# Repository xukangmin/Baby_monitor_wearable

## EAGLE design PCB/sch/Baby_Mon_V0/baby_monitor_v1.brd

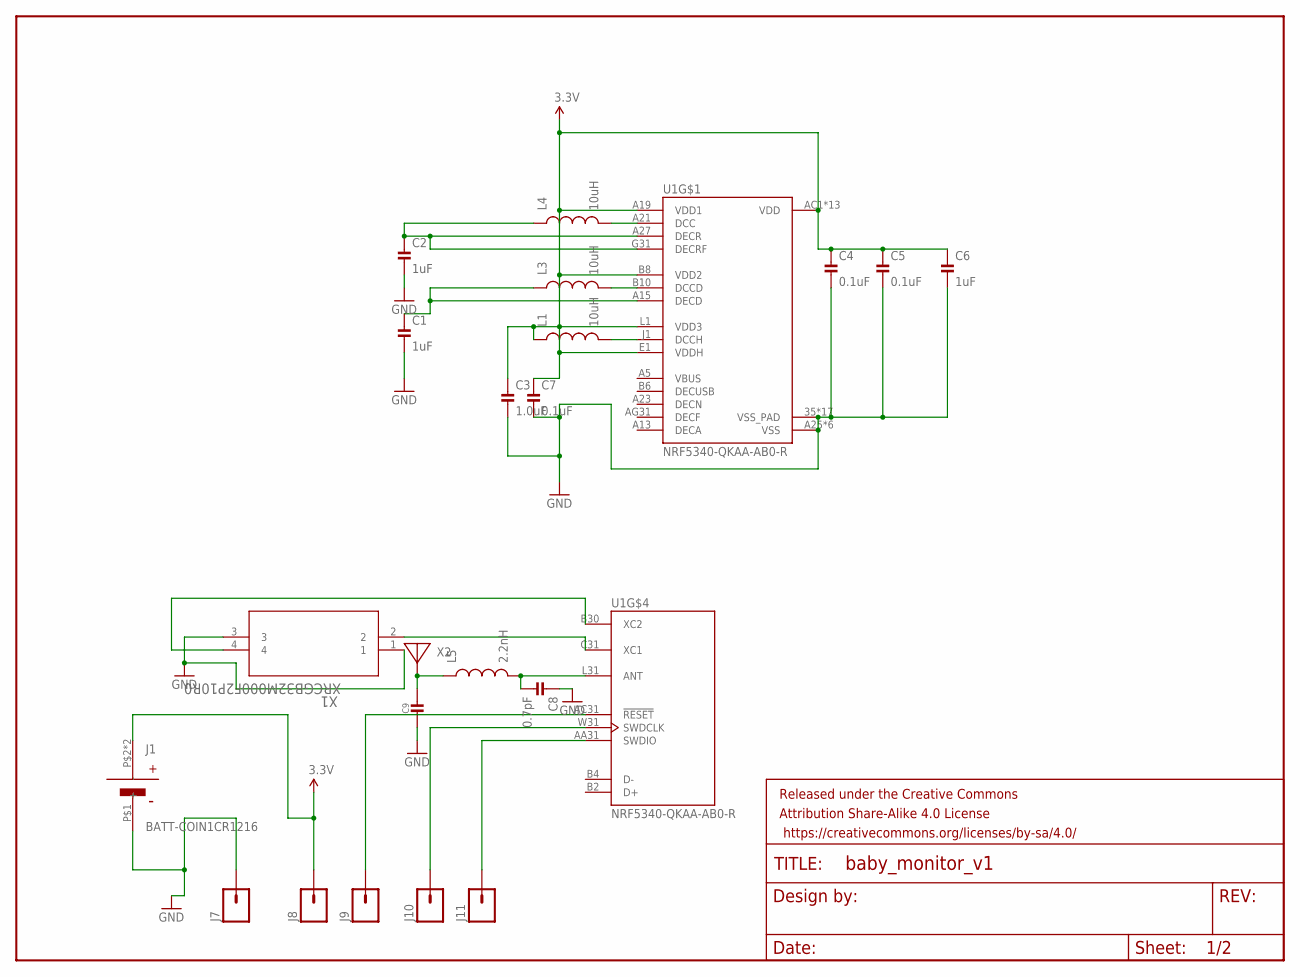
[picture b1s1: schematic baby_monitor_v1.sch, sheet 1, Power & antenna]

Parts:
C1, C2, C6: 1uF; MICROBUILDER__0402MP
C3: 1.0uF; MICROBUILDER__0402MP
C4, C5, C7: 0.1uF; MICROBUILDER__0402MP
C8: 0.7pF; MICROBUILDER__0402MP
C9: MICROBUILDER_CAP_CERAMIC_0402MP; MICROBUILDER__0402MP
FRAME1: FRAME-LETTERNO_PACKAGE; DUMMY
J1: BATT-COIN1CR1216; BC-2017-TR
J7, J8, J9, J10, J11: M01TINY; 1X01_TINY
L1, L3, L4: 10uH; NORDIC_MISC_RESC0603_N
L5: 2.2nH; NORDIC_MISC_RESC0402_N
U1: NRF5340-QKAA-AB0-R; XCVR_NRF5340-QKAA-AB0-R
X1: XRCGB32M000F2P10R0; XTAL_SON4_1P6X2P0_MUR
X2: ADAFRUIT_WIRELESS_ANTENNA_JOHANSON_2450AT18B100; ADAFRUIT_WIRELESS_ANT_2450AT18B100

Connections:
3.3V: C3.1, C4.1, C5.1, C6.1, C7.1, J1.P$2 (+), J1.P$3 (+), J8.P$1, L1.1, U1.A19 (VDD1), U1.AC1 (VDD), U1.AG1 (VDD), U1.AJ31 (VDD), U1.AL3 (VDD), U1.AL7 (VDD), U1.AL11 (VDD), U1.AL17 (VDD), U1.AL25 (VDD), U1.B8 (VDD2), U1.B28 (VDD), U1.C1 (VDD), U1.E1 (VDDH), U1.E31 (VDD), U1.L1 (VDD3), U1.N31 (VDD), U1.U1 (VDD); also elsewhere on the board
DECA: U1.A13 (DECA)
DECF: U1.AG31 (DECF)
DECN: U1.A23 (DECN)
DECUSB: U1.B6 (DECUSB)
GND: C1.2, C2.2, C3.2, C4.2, C5.2, C6.2, C7.2, C8.1, C9.2, J1.P$1 (-), J7.P$1, U1.35 (VSS_PAD), U1.36 (VSS_PAD), U1.37 (VSS_PAD), U1.38 (VSS_PAD), U1.39 (VSS_PAD), U1.40 (VSS_PAD), U1.41 (VSS_PAD), U1.43 (VSS_PAD), U1.44 (VSS_PAD), U1.45 (VSS_PAD), U1.46 (VSS_PAD), U1.47 (VSS_PAD), U1.48 (VSS_PAD), U1.49 (VSS_PAD), U1.50 (VSS_PAD), U1.51 (VSS_PAD), U1.104 (VSS_PAD), U1.A25 (VSS), U1.B12 (VSS), U1.B26 (VSS), U1.G1 (VSS), U1.H2 (VSS), U1.J31 (VSS), X1.1, X1.3; also elsewhere on the board
unnamed: L4.2, U1.A21 (DCC)
unnamed: L1.2, U1.J1 (DCCH)
unnamed: L3.2, U1.B10 (DCCD)
unnamed: C2.1, L4.1, U1.A27 (DECR), U1.G31 (DECRF)
unnamed: C1.1, L3.1, U1.A15 (DECD)
unnamed: U1.C31 (XC1), X1.2
unnamed: U1.B30 (XC2), X1.4
unnamed: C8.2, L5.2, U1.L31 (ANT)
unnamed: C9.1, L5.1, X2.FP
RESET: J9.P$1, U1.AC31 (!RESET)
SWDCLK: J10.P$1, U1.W31 (SWDCLK)
SWDIO: J11.P$1, U1.AA31 (SWDIO)
VBUS: U1.A5 (VBUS)

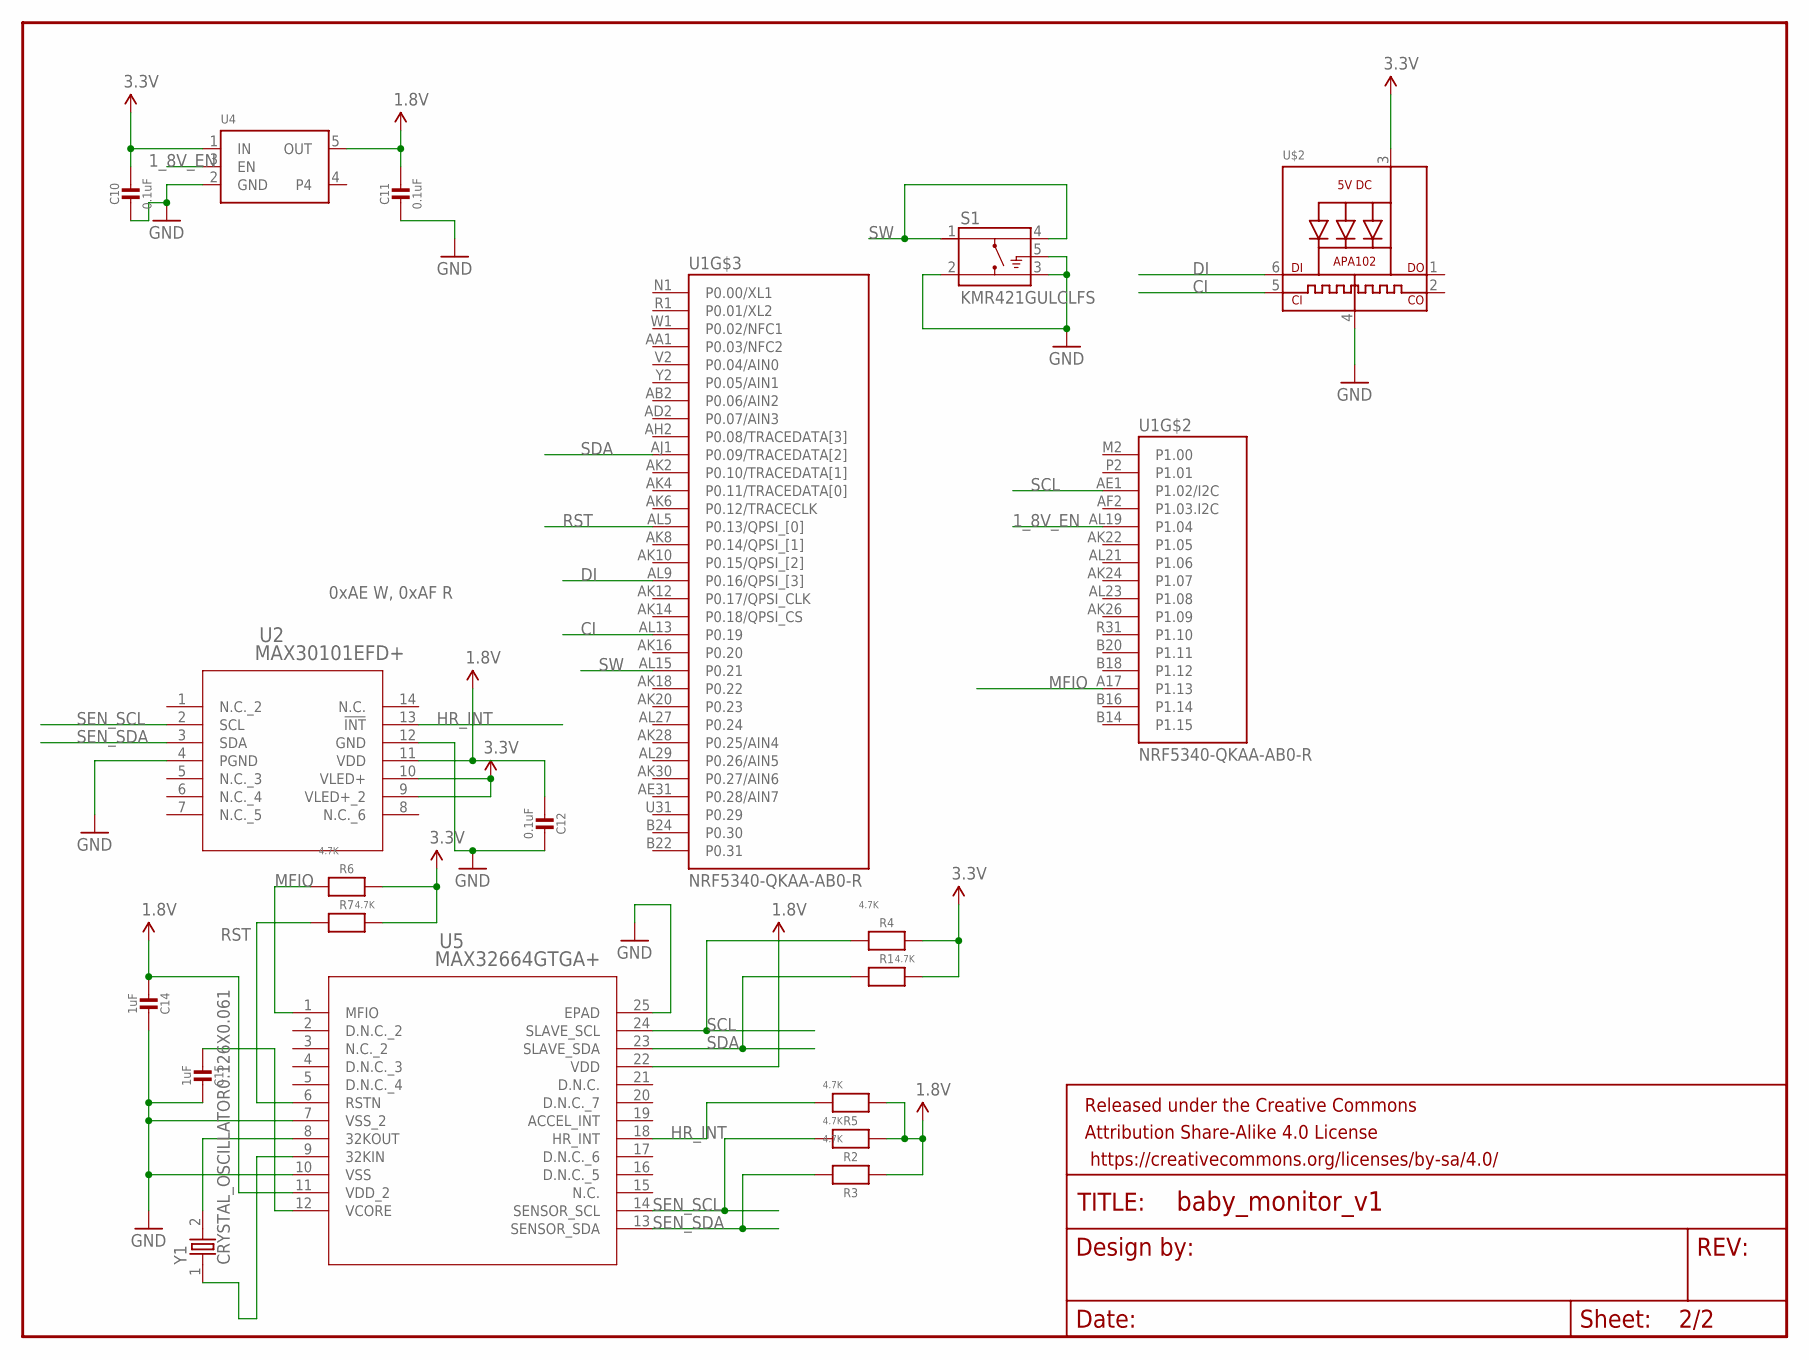
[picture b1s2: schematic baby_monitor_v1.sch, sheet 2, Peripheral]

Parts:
C10, C11, C12: 0.1uF; MICROBUILDER__0402MP
C14, C15: 1uF; MICROBUILDER__0402MP
FRAME2: FRAME-LETTERNO_PACKAGE; DUMMY
R1, R2, R3, R4, R5, R6, R7: 4.7K; MICROBUILDER__0402MP
S1: KMR421GULCLFS; SW_KMR421GULCLFS
U1: NRF5340-QKAA-AB0-R; XCVR_NRF5340-QKAA-AB0-R
U2: MAX30101EFD+; 21-0880B_MXM
U4: MICROBUILDER_VREG_SOT23-5; MICROBUILDER_SOT23-5
U5: MAX32664GTGA+; 21-100264_90-100089_MXM
U$2: MICROBUILDER_APA1022020; MICROBUILDER_APA102_2020
Y1: CRYSTAL_OSCILLATOR0.126X0.061; QUARTZ

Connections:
1.8V: C11.1, C12.2, C14.2, R2.1, R3.1, R5.1, U2.11 (VDD), U4.5 (OUT), U5.11 (VDD_2), U5.22 (VDD)
1_8V_EN: U1.AL19 (P1.04), U4.3 (EN)
3.3V: C10.1, R1.2, R4.2, R6.2, R7.2, U2.9 (VLED+_2), U2.10 (VLED+), U4.1 (IN), U$2.3 (VDD); also elsewhere on the board
CI: U1.AL13 (P0.19), U$2.5 (CKI)
DECA: U1.A13 (DECA)
DECF: U1.AG31 (DECF)
DECN: U1.A23 (DECN)
DECUSB: U1.B6 (DECUSB)
DI: U1.AL9 (P0.16/QPSI_[3]), U$2.6 (DI)
GND: C10.2, C11.2, C12.1, C14.1, C15.1, S1.2, S1.3, S1.5 (G), U2.4 (PGND), U2.12 (GND), U4.2 (GND), U5.7 (VSS_2), U5.10 (VSS), U5.25 (EPAD), U$2.4 (GND); also elsewhere on the board
HR_INT: R5.2, U2.13 (!INT), U5.18 (HR_INT)
MFIO: R6.1, U1.A17 (P1.13), U5.1 (MFIO)
unnamed: C15.2, U5.12 (VCORE)
unnamed: U5.8 (32KOUT), Y1.2
unnamed: U5.9 (32KIN), Y1.1
RST: R7.1, U1.AL5 (P0.13/QPSI_[0]), U5.6 (RSTN)
SCL: R4.1, U1.AE1 (P1.02/I2C), U5.24 (SLAVE_SCL)
SDA: R1.1, U1.AJ1 (P0.09/TRACEDATA[2]), U5.23 (SLAVE_SDA)
SEN_SCL: R2.2, U2.2 (SCL), U5.14 (SENSOR_SCL)
SEN_SDA: R3.2, U2.3 (SDA), U5.13 (SENSOR_SDA)
SW: S1.1, S1.4, U1.AL15 (P0.21)
VBUS: U1.A5 (VBUS)

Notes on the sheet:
0xAE W, 0xAF R

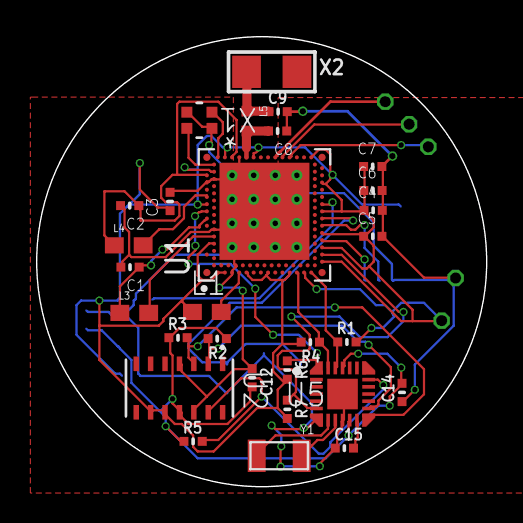
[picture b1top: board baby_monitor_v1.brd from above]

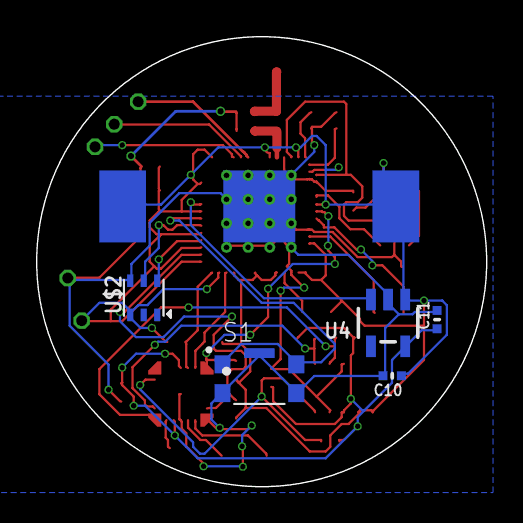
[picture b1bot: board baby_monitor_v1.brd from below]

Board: 2 copper layers, 25.0 x 25.0 mm, 42 parts (6 on the bottom side), 29 nets.

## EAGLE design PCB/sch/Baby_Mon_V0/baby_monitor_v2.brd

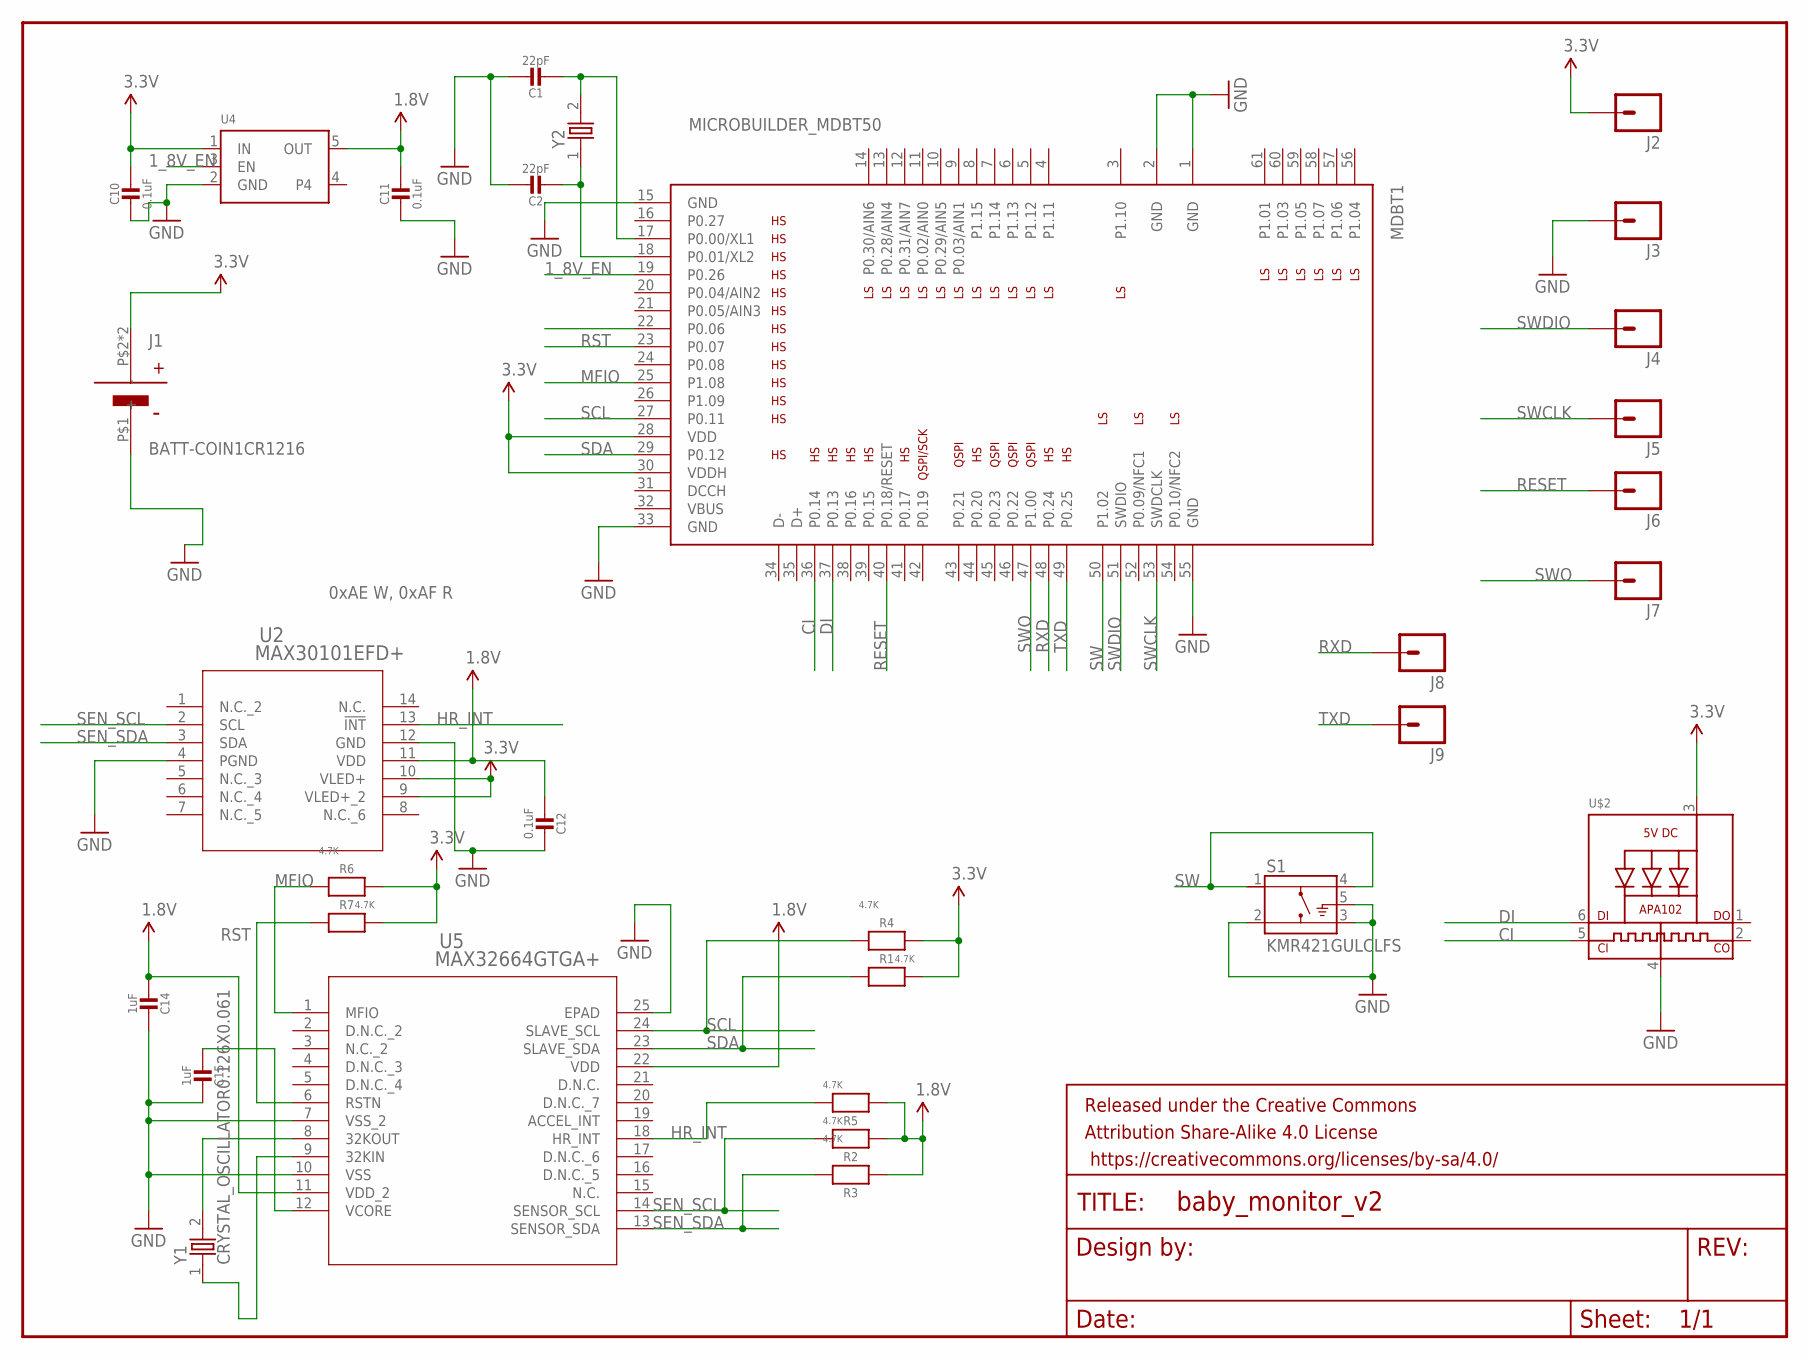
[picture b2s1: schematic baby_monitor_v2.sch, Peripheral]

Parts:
C1, C2: 22pF; MICROBUILDER__0402MP
C10, C11, C12: 0.1uF; MICROBUILDER__0402MP
C14, C15: 1uF; MICROBUILDER__0402MP
FRAME2: FRAME-LETTERNO_PACKAGE; DUMMY
J1: BATT-COIN1CR1216; BC-2017-TR
J2, J3, J4, J5, J6, J7: M01TINY; 1X01_TINY
J8, J9: M01TINY_SMD_EXT; 1X01_SMD_TINY_EXT
MDBT1: MICROBUILDER_MDBT50
R1, R2, R3, R4, R5, R6, R7: 4.7K; MICROBUILDER__0402MP
S1: KMR421GULCLFS; SW_KMR421GULCLFS
U2: MAX30101EFD+; 21-0880B_MXM
U4: MICROBUILDER_VREG_SOT23-5; MICROBUILDER_SOT23-5
U5: MAX32664GTGA+; 21-100264_90-100089_MXM
U$2: MICROBUILDER_APA1022020; MICROBUILDER_APA102_2020
Y1, Y2: CRYSTAL_OSCILLATOR0.126X0.061; QUARTZ

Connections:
1.8V: C11.1, C12.2, C14.2, R2.1, R3.1, R5.1, U2.11 (VDD), U4.5 (OUT), U5.11 (VDD_2), U5.22 (VDD)
1_8V_EN: MDBT1.19 (P0.26), U4.3 (EN)
3.3V: C10.1, J1.P$2 (+), J1.P$3 (+), J2.P$1, MDBT1.28 (VDD), MDBT1.30 (VDDH), R1.2, R4.2, R6.2, R7.2, U2.9 (VLED+_2), U2.10 (VLED+), U4.1 (IN), U$2.3 (VDD)
CI: MDBT1.36 (P0.14), U$2.5 (CKI)
DI: MDBT1.37 (P0.13), U$2.6 (DI)
GND: C1.1, C2.1, C10.2, C11.2, C12.1, C14.1, C15.1, J1.P$1 (-), J3.P$1, MDBT1.1 (GND), MDBT1.2 (GND), MDBT1.15 (GND), MDBT1.33 (GND), MDBT1.55 (GND), S1.2, S1.3, S1.5 (G), U2.4 (PGND), U2.12 (GND), U4.2 (GND), U5.7 (VSS_2), U5.10 (VSS), U5.25 (EPAD), U$2.4 (GND)
HR_INT: R5.2, U2.13 (!INT), U5.18 (HR_INT)
MFIO: MDBT1.25 (P1.08), R6.1, U5.1 (MFIO)
unnamed: C1.2, MDBT1.17 (P0.00/XL1), Y2.2
unnamed: C2.2, MDBT1.18 (P0.01/XL2), Y2.1
unnamed: C15.2, U5.12 (VCORE)
unnamed: U5.8 (32KOUT), Y1.2
unnamed: U5.9 (32KIN), Y1.1
RESET: J6.P$1, MDBT1.40 (P0.18/RESET)
RST: MDBT1.23 (P0.07), R7.1, U5.6 (RSTN)
RXD: J8.P$1, MDBT1.48 (P0.24)
SCL: MDBT1.27 (P0.11), R4.1, U5.24 (SLAVE_SCL)
SDA: MDBT1.29 (P0.12), R1.1, U5.23 (SLAVE_SDA)
SEN_SCL: R2.2, U2.2 (SCL), U5.14 (SENSOR_SCL)
SEN_SDA: R3.2, U2.3 (SDA), U5.13 (SENSOR_SDA)
SW: MDBT1.50 (P1.02), S1.1, S1.4
SWCLK: J5.P$1, MDBT1.53 (SWDCLK)
SWDIO: J4.P$1, MDBT1.51 (SWDIO)
SWO: J7.P$1, MDBT1.47 (P1.00)
TXD: J9.P$1, MDBT1.49 (P0.25)

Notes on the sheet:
0xAE W, 0xAF R

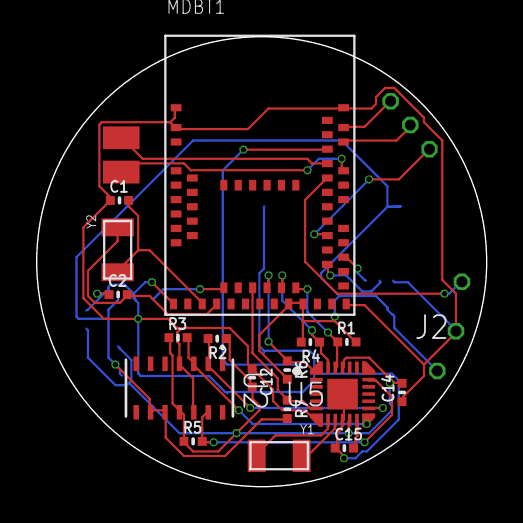
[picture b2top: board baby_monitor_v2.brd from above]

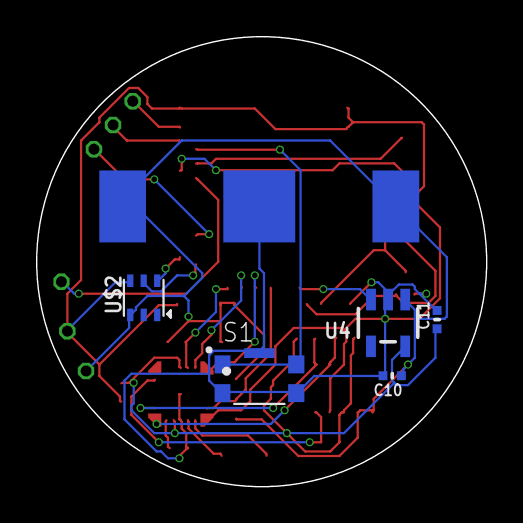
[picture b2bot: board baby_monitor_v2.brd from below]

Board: 2 copper layers, 25.0 x 25.0 mm, 32 parts (6 on the bottom side), 25 nets.

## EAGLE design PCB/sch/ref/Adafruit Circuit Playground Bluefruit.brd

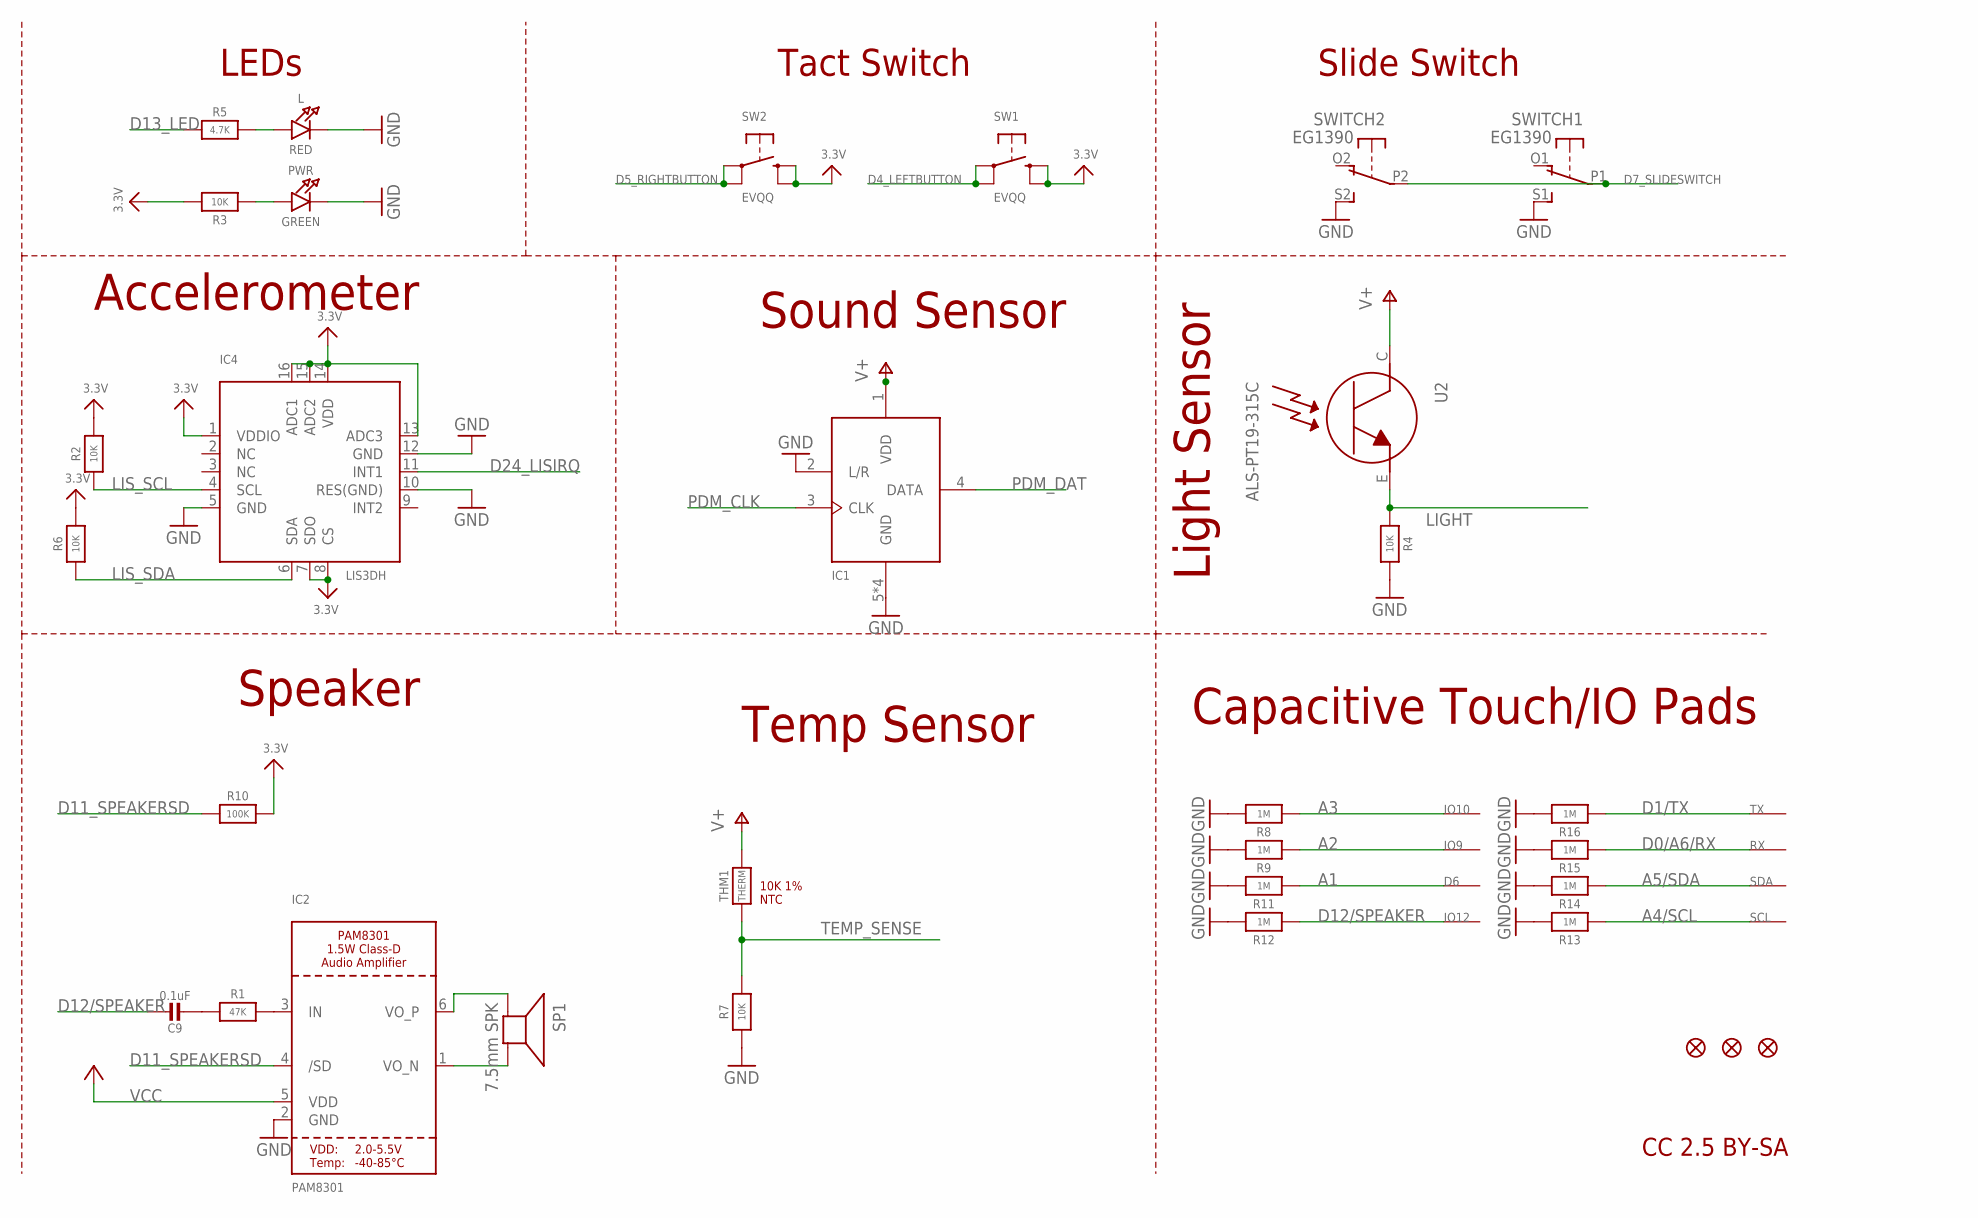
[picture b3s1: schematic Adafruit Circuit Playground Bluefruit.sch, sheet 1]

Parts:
C9: 0.1uF; 0603-NO
D6: SEWTAP-ALLIGATOR; SEWALLI
IC1: MIC_PDM; SPK0415HM4H
IC2: PAM8301; SOT23-6
IC4: LIS3DH; LGA16_3X3MM
IO9, IO10, IO12: SEWTAP-ALLIGATOR; SEWALLI
L: RED; CHIPLED_0603_NOOUTLINE
PWR: GREEN; CHIPLED_0603_NOOUTLINE
R1: 47K; 0603-NO
R2, R3, R4, R6, R7: 10K; 0603-NO
R5: 4.7K; 0603-NO
R8, R9, R11, R12, R13, R14, R15, R16: 1M; 0603-NO
R10: 100K; 0603-NO
RX: SEWTAP-ALLIGATOR; SEWALLI
SCL: SEWTAP-ALLIGATOR; SEWALLI
SDA: SEWTAP-ALLIGATOR; SEWALLI
SP1: 7.5mm SPK; BUZZER_SMT_7.5MM
SW1, SW2: EVQQ; EVQ-Q2_SMALLER
SWITCH: EG1390
THM1: THERM; _0402
TX: SEWTAP-ALLIGATOR; SEWALLI
U2: ALS-PT19-315C
U$2, U$3, U$6: FIDUCIAL_1MM

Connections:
3.3V: IC4.1 (VDDIO), IC4.7 (SDO), IC4.8 (CS), IC4.13 (ADC3), IC4.14 (VDD), IC4.15 (ADC2), IC4.16 (ADC1), R2.2, R3.2, R6.2, R10.2, SW1.B (S), SW1.B' (S1), SW2.B (S), SW2.B' (S1); also elsewhere on the board
A1: D6.P$1, R11.1; also elsewhere on the board
A2: IO9.P$1, R9.1; also elsewhere on the board
A3: IO10.P$1, R8.1; also elsewhere on the board
A4/SCL: R13.1, SCL.P$1; also elsewhere on the board
A5/SDA: R14.1, SDA.P$1; also elsewhere on the board
D0/A6/RX: R15.1, RX.P$1; also elsewhere on the board
D1/TX: R16.1, TX.P$1; also elsewhere on the board
D4_LEFTBUTTON: SW1.A, SW1.A' (P1); also elsewhere on the board
D5_RIGHTBUTTON: SW2.A, SW2.A' (P1); also elsewhere on the board
D7_SLIDESWITCH: SWITCH.P1, SWITCH.P2; also elsewhere on the board
D11_SPEAKERSD: IC2.4 (/SD), R10.1; also elsewhere on the board
D12/SPEAKER: C9.1, IO12.P$1, R12.1; also elsewhere on the board
D13_LED: R5.1; also elsewhere on the board
D24_LISIRQ: IC4.11 (INT1); also elsewhere on the board
GND: IC1.2 (L/R), IC1.5 (GND), IC1.6 (GND), IC1.7 (GND), IC1.8 (GND), IC2.2 (GND), IC4.5 (GND), IC4.10 (RES(GND)), IC4.12 (GND), L.C, PWR.C, R4.1, R7.1, R8.2, R9.2, R11.2, R12.2, R13.2, R14.2, R15.2, R16.2, SWITCH.S1 (S), SWITCH.S2 (S); also elsewhere on the board
LIGHT: R4.2, U2.E; also elsewhere on the board
LIS_SCL: IC4.4 (SCL), R2.1; also elsewhere on the board
LIS_SDA: IC4.6 (SDA), R6.1; also elsewhere on the board
unnamed: PWR.A, R3.1
unnamed: C9.2, R1.1
unnamed: IC2.3 (IN), R1.2
unnamed: IC2.6 (VO_P), SP1.+
unnamed: L.A, R5.2
unnamed: IC2.1 (VO_N), SP1.-
PDM_CLK: IC1.3 (CLK); also elsewhere on the board
PDM_DAT: IC1.4 (DATA); also elsewhere on the board
TEMP_SENSE: R7.2, THM1.1; also elsewhere on the board
V+: IC1.1 (VDD), THM1.2, U2.C; also elsewhere on the board
VCC: IC2.5 (VDD); also elsewhere on the board

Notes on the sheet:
CC 2.5 BY-SA
10K 1% NTC
Speaker
Temp Sensor
Light Sensor
Sound Sensor
Slide Switch
Tact Switch
LEDs
Accelerometer
Capacitive Touch/IO Pads

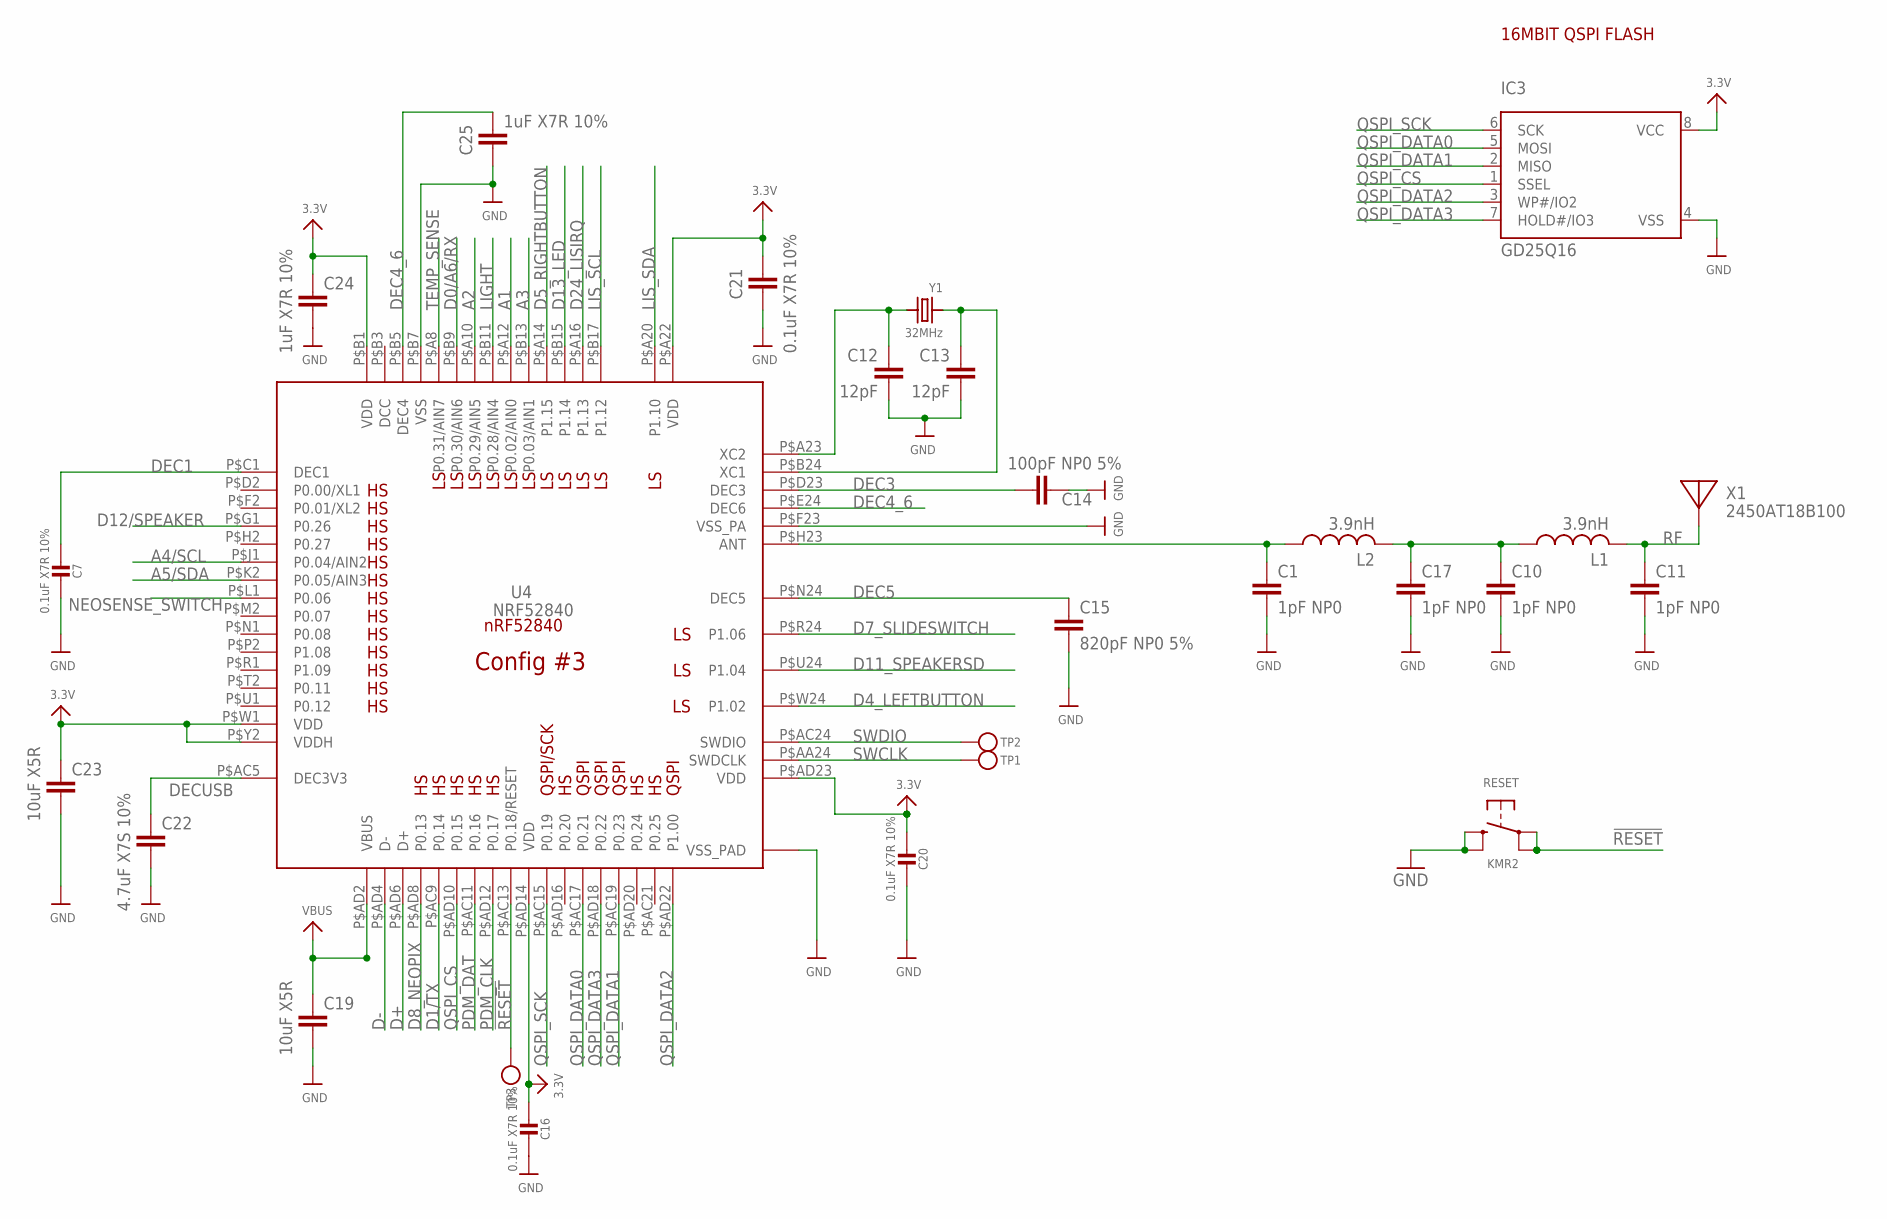
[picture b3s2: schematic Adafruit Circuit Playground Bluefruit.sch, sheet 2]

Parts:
C1, C10, C11, C17: 1pF NP0; RESC0402_N
C7, C16, C20: 0.1uF X7R 10%; 0603-NO
C12, C13: 12pF; RESC0402_N
C14: 100pF NP0 5%; RESC0402_N
C15: 820pF NP0 5%; RESC0402_N
C19, C23: 10uF X5R; RESC0805_N
C21: 0.1uF X7R 10%; RESC0603_L
C22: 4.7uF X7S 10%; RESC0805_N
C24, C25: 1uF X7R 10%; RESC0603_N
IC3: GD25Q16; USON8
L1, L2: 3.9nH; RESC0402_N
RESET: KMR2; BTN_KMR2_4.6X2.8
TP1, TP2, TP3: TESTPOINTROUND1.5MMNO; TESTPOINT_ROUND_1.5MM_NO
U4: NRF52840; AQFN50P700X800X85_HS-74N_SMALLCENTER
X1: 2450AT18B100; ANT_2450AT18B100
Y1: 32MHz; CRYSTAL_2X1.6

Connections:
3.3V: C16.2, C20.2, C21.1, C23.1, C24.1, IC3.8 (VCC), U4.P$A22 (VDD), U4.P$AD14 (VDD), U4.P$AD23 (VDD), U4.P$B1 (VDD), U4.P$W1 (VDD), U4.P$Y2 (VDDH); also elsewhere on the board
!RESET: RESET.A, RESET.A' (P1), TP3.P$1, U4.P$AC13 (P0.18/RESET)
A1: U4.P$A12 (P0.02/AIN0); also elsewhere on the board
A2: U4.P$A10 (P0.29/AIN5); also elsewhere on the board
A3: U4.P$B13 (P0.03/AIN1); also elsewhere on the board
A4/SCL: U4.P$J1 (P0.04/AIN2); also elsewhere on the board
A5/SDA: U4.P$K2 (P0.05/AIN3); also elsewhere on the board
D0/A6/RX: U4.P$B9 (P0.30/AIN6); also elsewhere on the board
D1/TX: U4.P$AC9 (P0.14); also elsewhere on the board
D4_LEFTBUTTON: U4.P$W24 (P1.02); also elsewhere on the board
D5_RIGHTBUTTON: U4.P$A14 (P1.15); also elsewhere on the board
D7_SLIDESWITCH: U4.P$R24 (P1.06); also elsewhere on the board
D8_NEOPIX: U4.P$AD8 (P0.13); also elsewhere on the board
D11_SPEAKERSD: U4.P$U24 (P1.04); also elsewhere on the board
D12/SPEAKER: U4.P$G1 (P0.26); also elsewhere on the board
D13_LED: U4.P$B15 (P1.14); also elsewhere on the board
D24_LISIRQ: U4.P$A16 (P1.13); also elsewhere on the board
D+: U4.P$AD6 (D+); also elsewhere on the board
D-: U4.P$AD4 (D-); also elsewhere on the board
DEC1: C7.2, U4.P$C1 (DEC1)
DEC3: C14.1, U4.P$D23 (DEC3)
DEC4_6: C25.1, U4.P$B5 (DEC4), U4.P$E24 (DEC6)
DEC5: C15.1, U4.P$N24 (DEC5)
DECUSB: C22.1, U4.P$AC5 (DEC3V3)
GND: C1.2, C7.1, C10.2, C11.2, C12.2, C13.2, C14.2, C15.2, C16.1, C17.2, C19.2, C20.1, C21.2, C22.2, C23.2, C24.2, C25.2, IC3.4 (VSS), RESET.B (S), RESET.B' (S1), U4.P$B7 (VSS), U4.P$F23 (VSS_PA), U4.THERMPAD (VSS_PAD); also elsewhere on the board
LIGHT: U4.P$B11 (P0.28/AIN4); also elsewhere on the board
LIS_SCL: U4.P$B17 (P1.12); also elsewhere on the board
LIS_SDA: U4.P$A20 (P1.10); also elsewhere on the board
unnamed: C1.1, L2.1, U4.P$H23 (ANT)
unnamed: C12.1, U4.P$A23 (XC2), Y1.3 (2)
unnamed: C13.1, U4.P$B24 (XC1), Y1.1
NEOSENSE_SWITCH: U4.P$L1 (P0.06); also elsewhere on the board
PDM_CLK: U4.P$AD12 (P0.17); also elsewhere on the board
PDM_DAT: U4.P$AC11 (P0.16); also elsewhere on the board
QSPI_CS: IC3.1 (SSEL), U4.P$AD10 (P0.15)
QSPI_DATA0: IC3.5 (MOSI), U4.P$AC17 (P0.21)
QSPI_DATA1: IC3.2 (MISO), U4.P$AC19 (P0.23)
QSPI_DATA2: IC3.3 (WP#/IO2), U4.P$AD22 (P1.00)
QSPI_DATA3: IC3.7 (HOLD#/IO3), U4.P$AD18 (P0.22)
QSPI_SCK: IC3.6 (SCK), U4.P$AC15 (P0.19)
RF: C11.1, L1.2, X1.FP
RF1: C10.1, C17.1, L1.1, L2.2
SWCLK: TP1.P$1, U4.P$AA24 (SWDCLK)
SWDIO: TP2.P$1, U4.P$AC24 (SWDIO)
TEMP_SENSE: U4.P$A8 (P0.31/AIN7); also elsewhere on the board
VBUS: C19.1, U4.P$AD2 (VBUS); also elsewhere on the board

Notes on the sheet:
16MBIT QSPI FLASH
Config #3

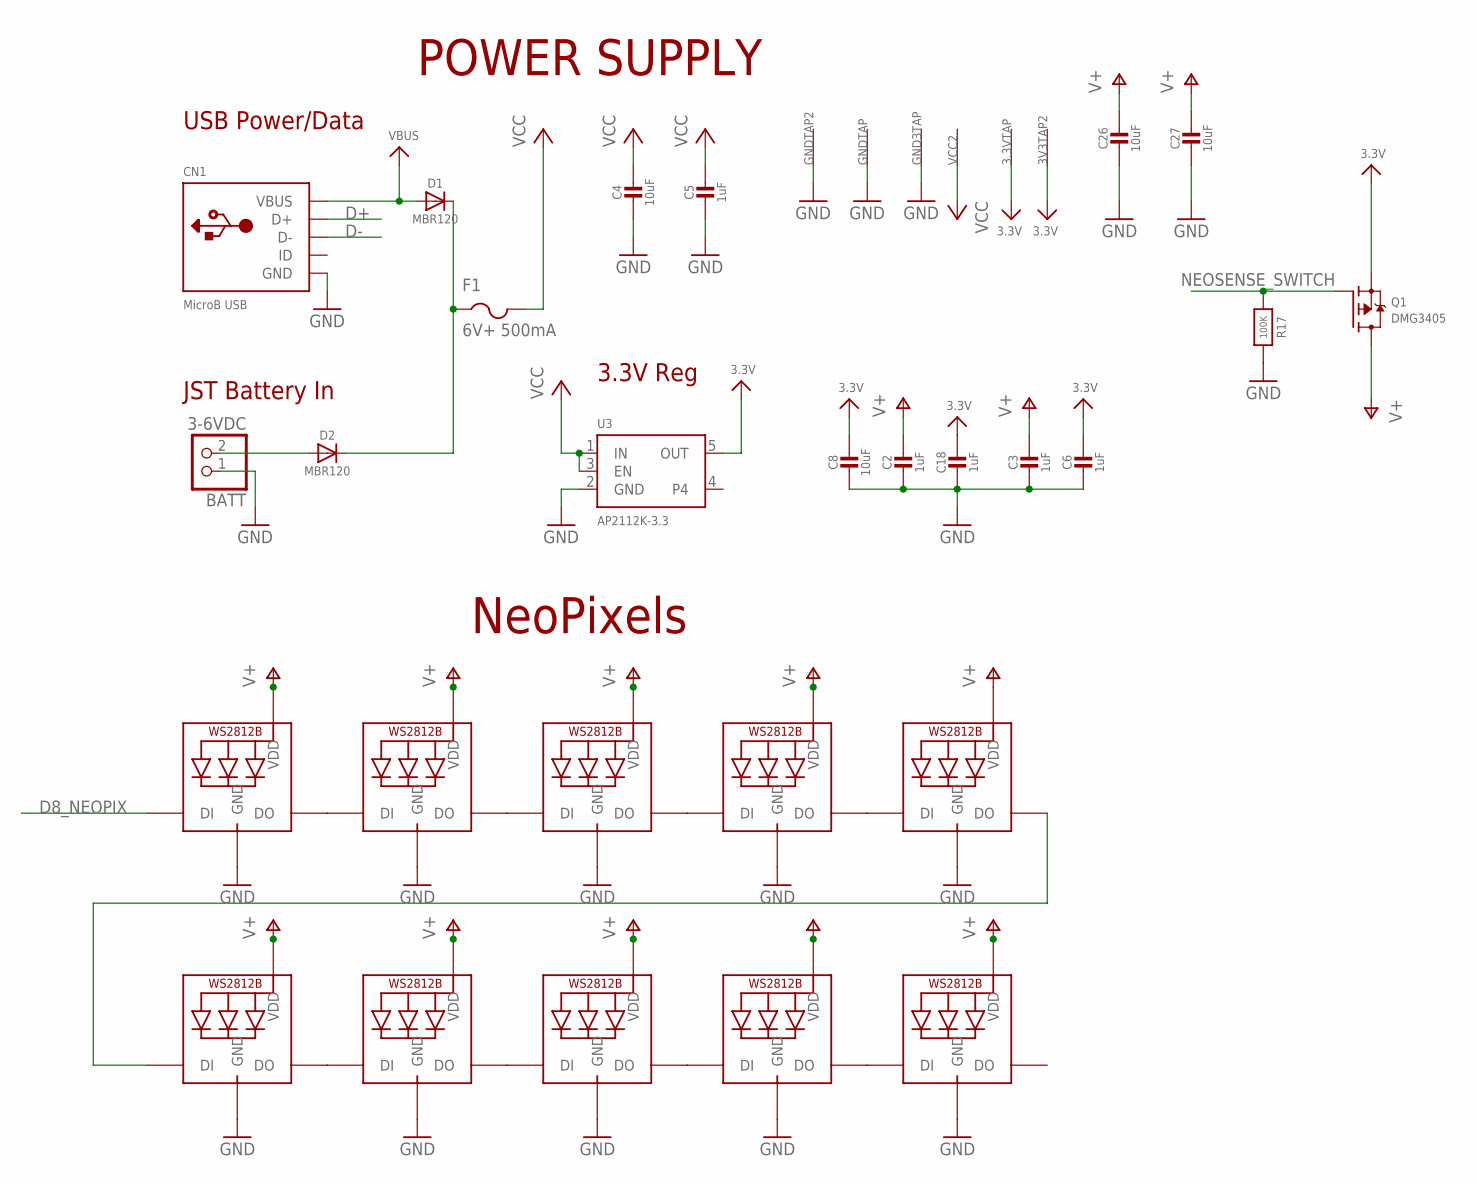
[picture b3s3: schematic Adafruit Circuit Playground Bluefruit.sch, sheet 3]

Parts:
3.3VTAP, 3V3TAP2: SEWTAP-ALLIGATOR; SEWALLI
BATT: 3-6VDC; JSTPH2
C2, C3, C5, C6, C18: 1uF; 0603-NO
C4, C8, C26, C27: 10uF; 0805-NO
CN1: MicroB USB; 4UCONN_20329_V2
D1, D2: MBR120; SOD-123
F1: 6V+ 500mA; R1206
GND3TAP: SEWTAP-ALLIGATOR; SEWALLI
GNDTAP, GNDTAP2: SEWTAP-ALLIGATOR; SEWALLI
LED1, LED2, LED3, LED4, LED5, LED6, LED7, LED8, LED9, LED10: WS2812B3535; LED3535
Q1: DMG3405; SOT23-R
R17: 100K; 0603-NO
U3: AP2112K-3.3; SOT23-5
VCC2: SEWTAP-ALLIGATOR; SEWALLI

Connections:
3.3V: 3.3VTAP.P$1, 3V3TAP2.P$1, C6.1, C8.1, C18.1, Q1.2 (S), U3.5 (OUT); also elsewhere on the board
D8_NEOPIX: LED6.1 (DI); also elsewhere on the board
D+: CN1.D+; also elsewhere on the board
D-: CN1.D-; also elsewhere on the board
GND: BATT.1, C2.2, C3.2, C4.2, C5.2, C6.2, C8.2, C18.2, C26.2, C27.2, CN1.BASE@1 (GND), CN1.BASE@2 (GND), CN1.GND, CN1.SPRT@1 (GND), CN1.SPRT@2 (GND), CN1.SPRT@3 (GND), CN1.SPRT@4 (GND), GND3TAP.P$1, GNDTAP.P$1, GNDTAP2.P$1, LED1.4 (GND), LED2.4 (GND), LED3.4 (GND), LED4.4 (GND), LED5.4 (GND), LED6.4 (GND), LED7.4 (GND), LED8.4 (GND), LED9.4 (GND), LED10.4 (GND), R17.2, U3.2 (GND); also elsewhere on the board
unnamed: D1.C, D2.C, F1.1
unnamed: BATT.2, D2.A
unnamed: LED1.1 (DI), LED2.3 (DO)
unnamed: LED1.3 (DO), LED3.1 (DI)
unnamed: LED2.1 (DI), LED10.3 (DO)
unnamed: LED6.3 (DO), LED7.1 (DI)
unnamed: LED7.3 (DO), LED8.1 (DI)
unnamed: LED8.3 (DO), LED9.1 (DI)
unnamed: LED9.3 (DO), LED10.1 (DI)
unnamed: LED3.3 (DO), LED4.1 (DI)
unnamed: LED4.3 (DO), LED5.1 (DI)
NEOSENSE_SWITCH: Q1.1 (G), R17.1; also elsewhere on the board
V+: C2.1, C3.1, C26.1, C27.1, LED1.2 (VDD), LED2.2 (VDD), LED3.2 (VDD), LED4.2 (VDD), LED5.2 (VDD), LED6.2 (VDD), LED7.2 (VDD), LED8.2 (VDD), LED9.2 (VDD), LED10.2 (VDD), Q1.3 (D); also elsewhere on the board
VBUS: CN1.VBUS, D1.A; also elsewhere on the board
VCC: C4.1, C5.1, F1.2, U3.1 (IN), U3.3 (EN), VCC2.P$1; also elsewhere on the board

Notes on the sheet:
NeoPixels
USB Power/Data
JST Battery In
3.3V Reg
POWER SUPPLY

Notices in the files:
parts and their libraries:
SparkFun-Aesthetics: Licensing: Creative Commons ShareAlike 4.0 International - https://creativecommons.org/licenses/by-sa/4.0
COPYRIGHT: Copyright (C) 2018 Accelerated Designs. All rights reserved
SparkFun-Aesthetics: Released under the Creative Commons Attribution Share-Alike 4.0 License
